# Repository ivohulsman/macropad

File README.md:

# Macropad V1
A Macropad built with KMK firmware.

**This is a work in progress.**  

### How to install firmware
1. Follow the KMK guide as shown [here](http://kmkfw.io/docs/Getting_Started).
2. Copy the files from /src to your Macropad overwriting existing files.
3. Customize keymaps and OLED to your usecase.

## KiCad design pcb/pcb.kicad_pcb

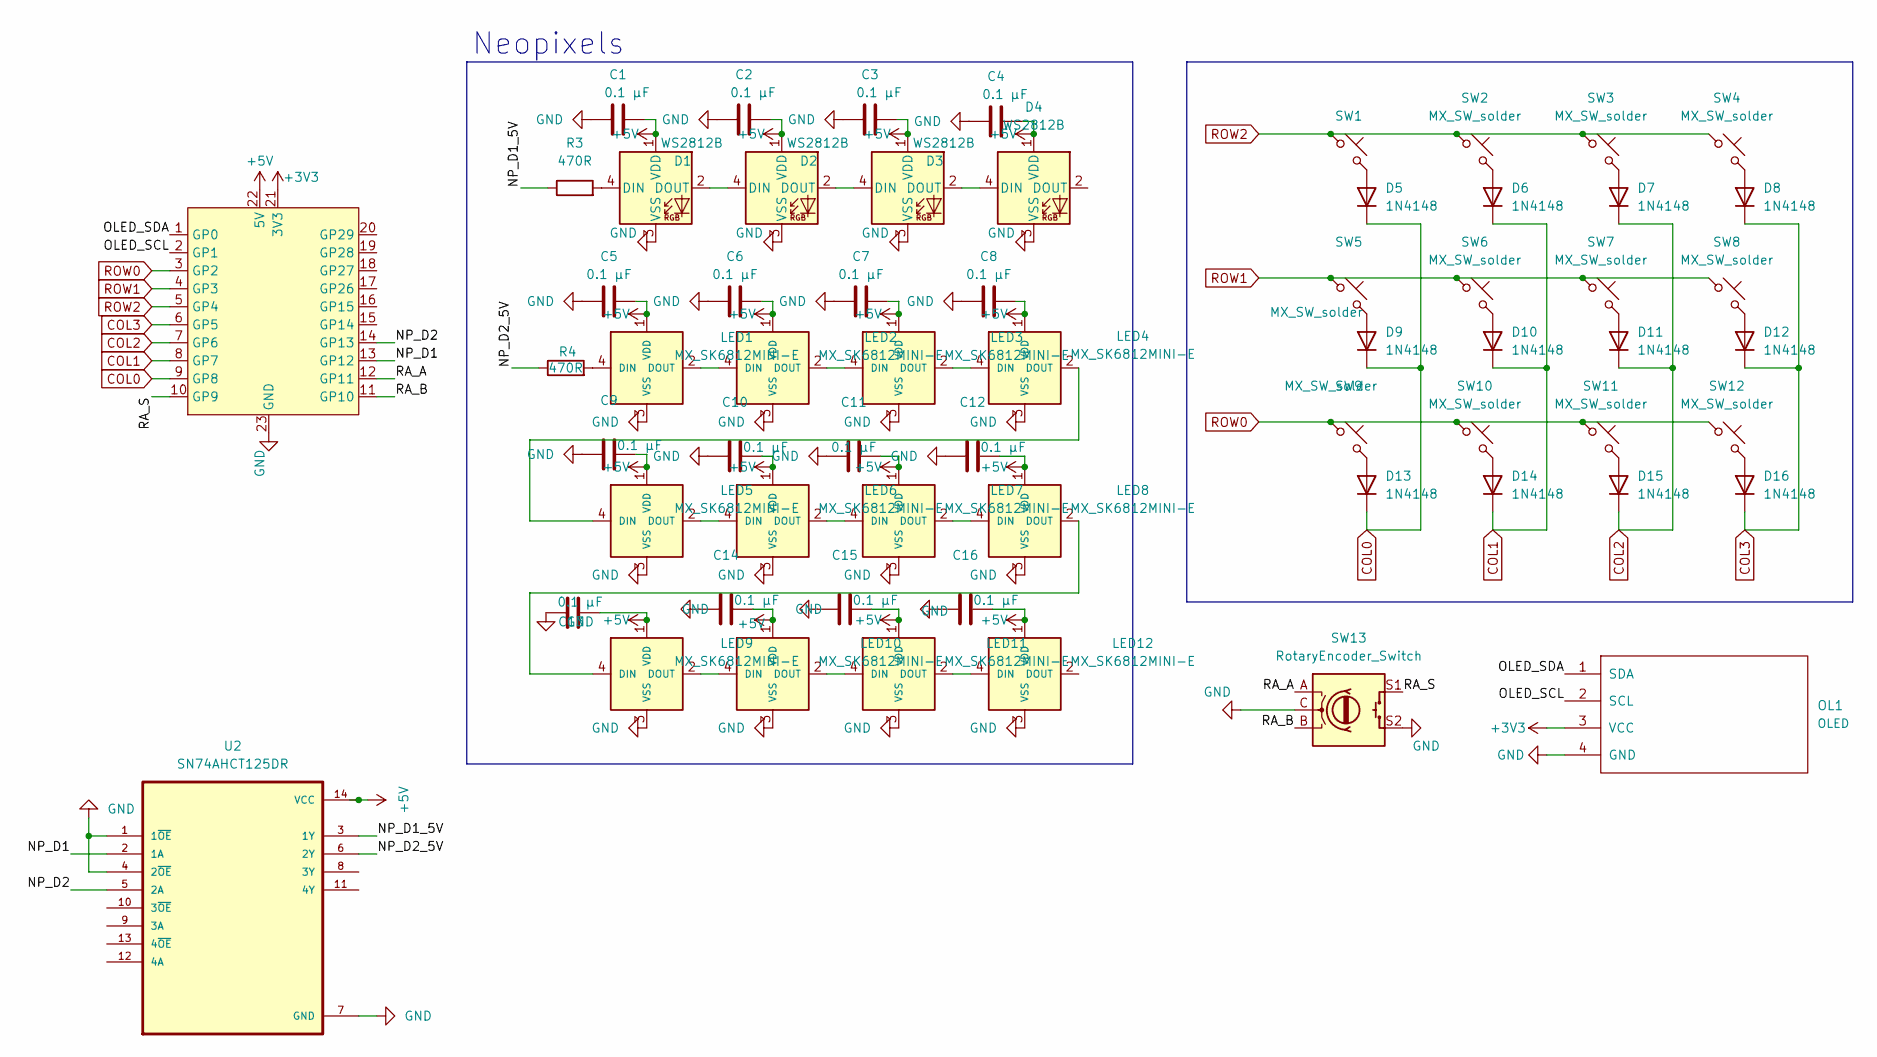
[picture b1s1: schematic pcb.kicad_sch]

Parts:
C1, C2, C3, C4, C5, C6, C7, C8, C9, C10, C11, C12, C13, C14, C15, C16: 0.1 µF; C_0603_1608Metric
D1, D2, D3, D4: WS2812B; LED_WS2812B_PLCC4_5.0x5.0mm_P3.2mm
D5, D6, D7, D8, D9, D10, D11, D12, D13, D14, D15, D16: 1N4148; D_DO-35_SOD27_P7.62mm_Horizontal
LED1, LED2, LED3, LED4, LED5, LED6, LED7, LED8, LED9, LED10, LED11, LED12: MX_SK6812MINI-E; SK6812-MINI-E
OL1: OLED; SSD1306_0.96_Oled
R3, R4: 470R; R_0603_1608Metric
SW1, SW2, SW3, SW4, SW5, SW6, SW7, SW8, SW9, SW10, SW11, SW12: MX_SW_solder; MX_ALPS_PG1350_noLed
SW13: RotaryEncoder_Switch; RotaryEncoder_EC11
U1: PicoW; RP2040-Zero
U2: SN74AHCT125DR; SOIC127P600X175-14N

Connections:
+3V3: OL1.3 (VCC), U1.21 (3V3)
+5V: C1.2, C2.2, C3.2, C4.2, C5.2, C6.2, C7.2, C8.2, C9.2, C10.2, C11.2, C12.2, C13.2, C14.2, C15.2, C16.2, D1.1 (VDD), D2.1 (VDD), D3.1 (VDD), D4.1 (VDD), LED1.1 (VDD), LED2.1 (VDD), LED3.1 (VDD), LED4.1 (VDD), LED5.1 (VDD), LED6.1 (VDD), LED7.1 (VDD), LED8.1 (VDD), LED9.1 (VDD), LED10.1 (VDD), LED11.1 (VDD), LED12.1 (VDD), U1.22 (5V), U2.14 (VCC)
/NP_D1: U1.13 (GP12), U2.2 (1A)
/NP_D1_5V: R3.1, U2.3 (1Y)
/NP_D2: U1.14 (GP13), U2.5 (2A)
/NP_D2_5V: R4.1, U2.6 (2Y)
/OLED_SCL: OL1.2 (SCL), U1.2 (GP1)
/OLED_SDA: OL1.1 (SDA), U1.1 (GP0)
/RA_A: SW13.A, U1.12 (GP11)
/RA_B: SW13.B, U1.11 (GP10)
/RA_S: SW13.S1, U1.10 (GP9)
COL0: D5.1 (K), D9.1 (K), D13.1 (K), U1.9 (GP8)
COL1: D6.1 (K), D10.1 (K), D14.1 (K), U1.8 (GP7)
COL2: D7.1 (K), D11.1 (K), D15.1 (K), U1.7 (GP6)
COL3: D8.1 (K), D12.1 (K), D16.1 (K), U1.6 (GP5)
GND: C1.1, C2.1, C3.1, C4.1, C5.1, C6.1, C7.1, C8.1, C9.1, C10.1, C11.1, C12.1, C13.1, C14.1, C15.1, C16.1, D1.3 (VSS), D2.3 (VSS), D3.3 (VSS), D4.3 (VSS), LED1.3 (VSS), LED2.3 (VSS), LED3.3 (VSS), LED4.3 (VSS), LED5.3 (VSS), LED6.3 (VSS), LED7.3 (VSS), LED8.3 (VSS), LED9.3 (VSS), LED10.3 (VSS), LED11.3 (VSS), LED12.3 (VSS), OL1.4 (GND), SW13.C, SW13.S2, U1.23 (GND), U2.1 (1~OE), U2.4 (2~OE), U2.7 (GND)
unnamed: D1.4 (DIN), R3.2
unnamed: D1.2 (DOUT), D2.4 (DIN)
unnamed: D2.2 (DOUT), D3.4 (DIN)
unnamed: D3.2 (DOUT), D4.4 (DIN)
unnamed: D5.2 (A), SW1.2
unnamed: D6.2 (A), SW2.2
unnamed: D7.2 (A), SW3.2
unnamed: D8.2 (A), SW4.2
unnamed: D9.2 (A), SW5.2
unnamed: D10.2 (A), SW6.2
unnamed: D11.2 (A), SW7.2
unnamed: D12.2 (A), SW8.2
unnamed: D13.2 (A), SW9.2
unnamed: D14.2 (A), SW10.2
unnamed: D15.2 (A), SW11.2
unnamed: D16.2 (A), SW12.2
unnamed: LED1.4 (DIN), R4.2
unnamed: LED1.2 (DOUT), LED2.4 (DIN)
unnamed: LED2.2 (DOUT), LED3.4 (DIN)
unnamed: LED3.2 (DOUT), LED4.4 (DIN)
unnamed: LED4.2 (DOUT), LED5.4 (DIN)
unnamed: LED5.2 (DOUT), LED6.4 (DIN)
unnamed: LED6.2 (DOUT), LED7.4 (DIN)
unnamed: LED7.2 (DOUT), LED8.4 (DIN)
unnamed: LED8.2 (DOUT), LED9.4 (DIN)
unnamed: LED9.2 (DOUT), LED10.4 (DIN)
unnamed: LED10.2 (DOUT), LED11.4 (DIN)
unnamed: LED11.2 (DOUT), LED12.4 (DIN)
ROW0: SW9.1, SW10.1, SW11.1, SW12.1, U1.3 (GP2)
ROW1: SW5.1, SW6.1, SW7.1, SW8.1, U1.4 (GP3)
ROW2: SW1.1, SW2.1, SW3.1, SW4.1, U1.5 (GP4)

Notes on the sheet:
Neopixels

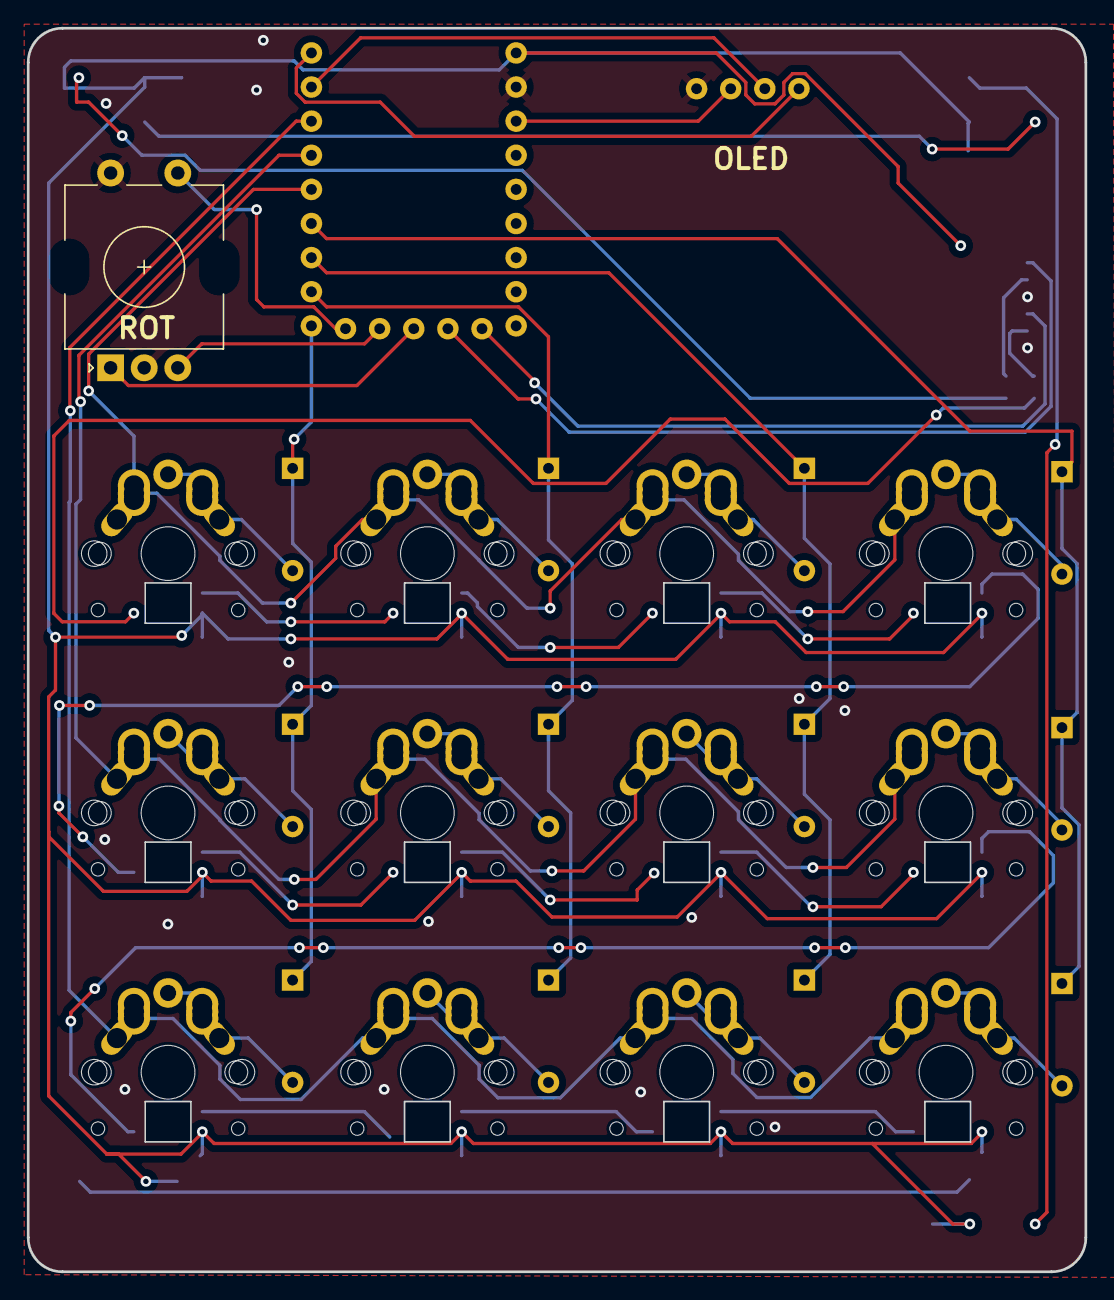
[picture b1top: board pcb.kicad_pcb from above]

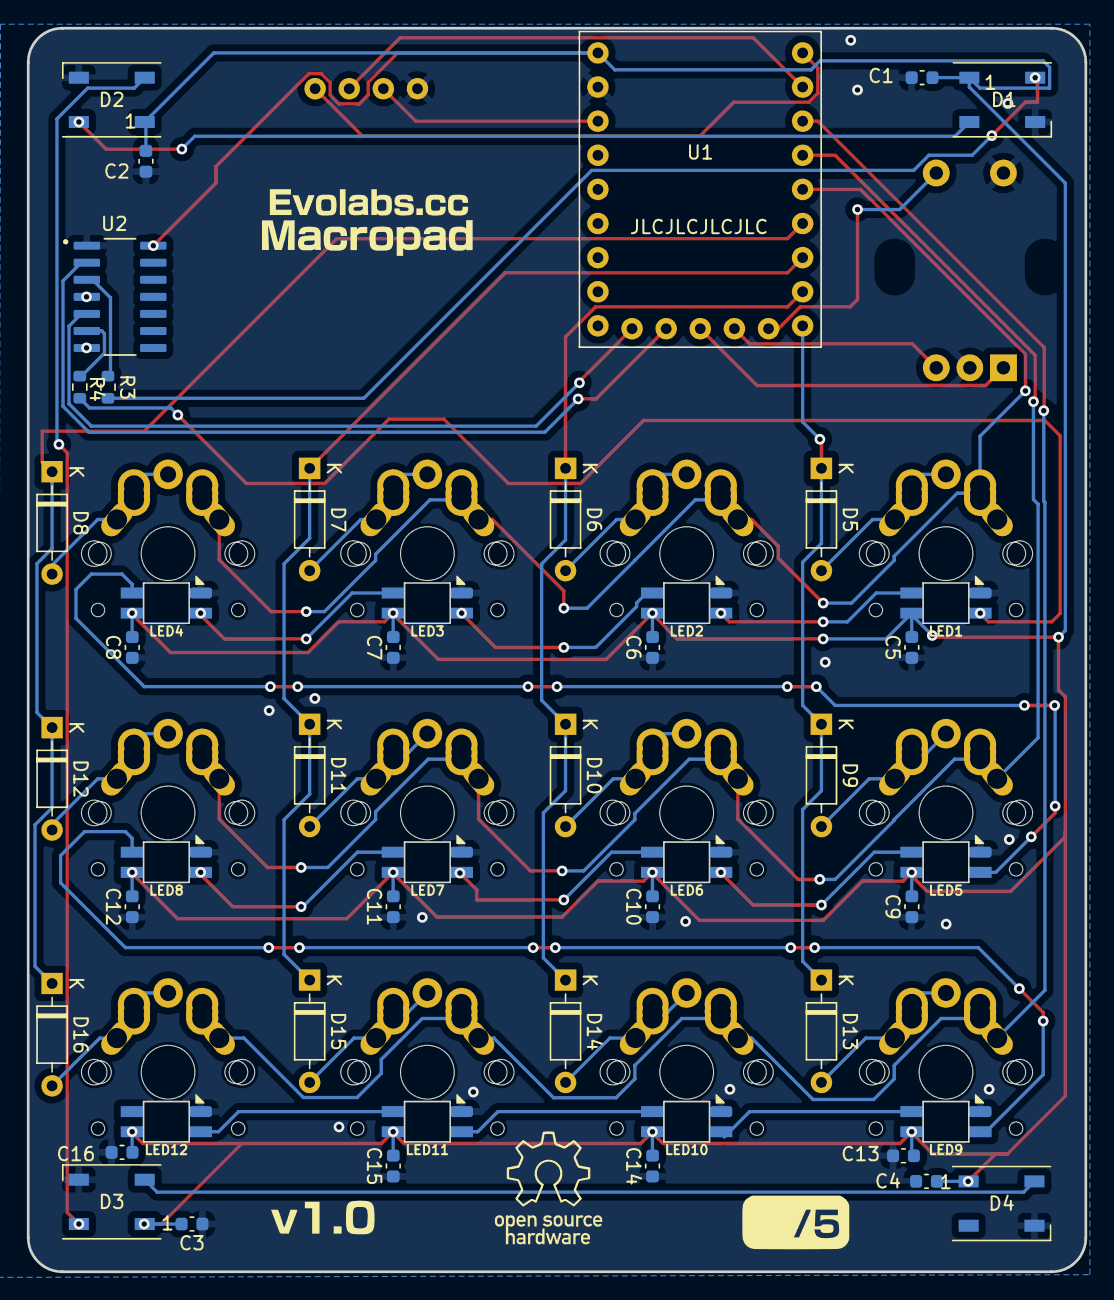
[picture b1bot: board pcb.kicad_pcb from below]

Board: 2 copper layers, 78.7 x 92.6 mm, 62 parts (49 on the bottom side), 47 nets.

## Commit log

2023-05-19 Initial installation guide
2023-05-26 Remove old i2c object from kb.py
